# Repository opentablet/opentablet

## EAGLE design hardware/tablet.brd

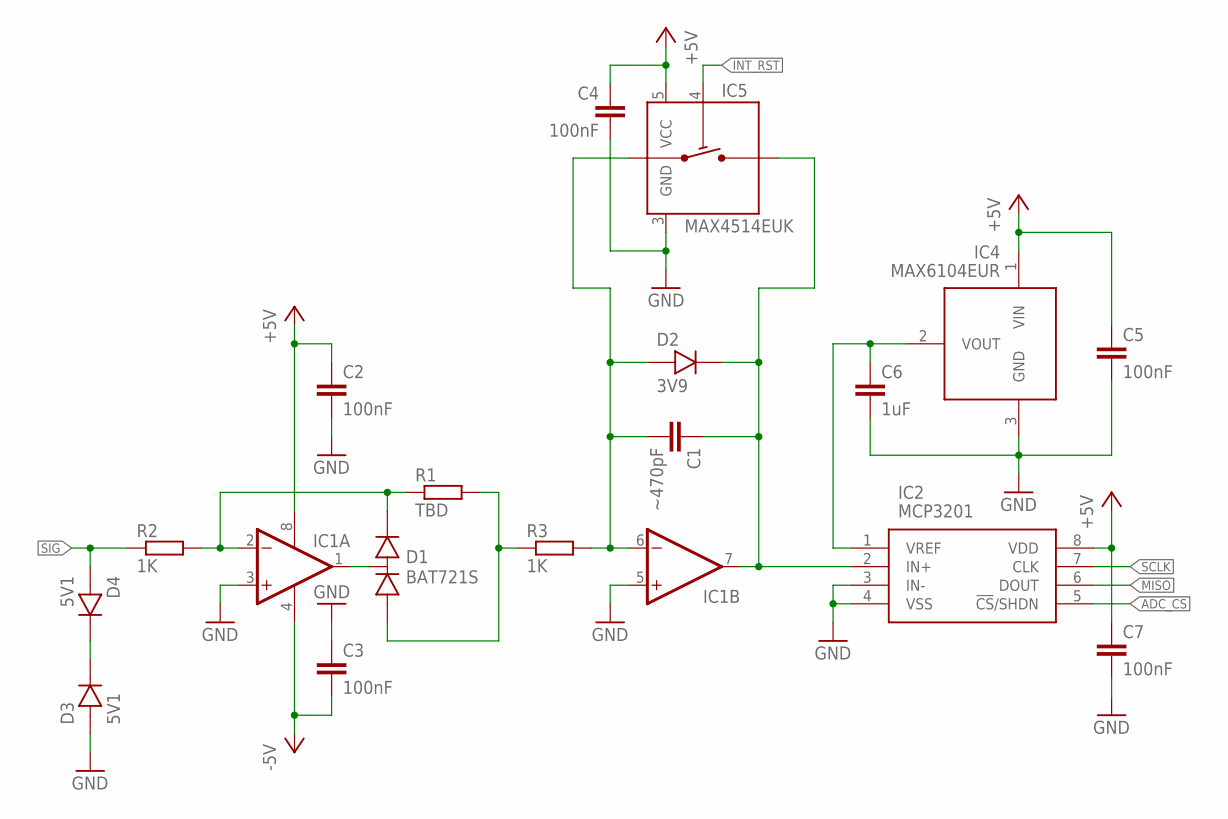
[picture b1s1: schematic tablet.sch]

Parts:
C1: ~470pF; 0603
C2, C3, C4, C5, C7: 100nF; 0603
C6: 1uF; 0603
D1: BAT721S; SOT23_3
D2: 3V9; SOD323
D3, D4: 5V1; SOD323
IC1: OPAMP_DUALSOIC8; SOIC8
IC2: MCP3201; SOIC8
IC4: MAX6104EUR; SOT23_3
IC5: MAX4514EUK; SOT23_5
R1: TBD; 0603
R2, R3: 1K; 0603

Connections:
+5V: C2.1, C4.1, C5.1, C7.1, IC1.8 (V+), IC2.8 (VDD), IC4.1 (VIN), IC5.5 (VCC)
-5V: C3.2, IC1.4 (V-)
ADC_CS: IC2.5 (!CS!/SHDN)
GND: C2.2, C3.1, C4.2, C5.2, C6.2, C7.2, D3.1, IC1.3 (+IN), IC1.5 (+IN), IC2.3 (IN-), IC2.4 (VSS), IC4.3 (GND), IC5.3 (GND)
INT_RST: IC5.4 (IN)
MISO: IC2.6 (DOUT)
unnamed: D1.1 (A), R1.2, R3.1
unnamed: D1.2 (C), IC1.2 (-IN), R1.1, R2.2
unnamed: D1.3 (COM), IC1.1 (OUT)
unnamed: C1.2, D2.1, IC1.6 (-IN), IC5.1 (COM), R3.2
unnamed: D3.2, D4.2
unnamed: C6.1, IC2.1 (VREF), IC4.2 (VOUT)
SCLK: IC2.7 (CLK)
SIG: D4.1, R2.1
VOUT: C1.1, D2.2, IC1.7 (OUT), IC2.2 (IN+), IC5.2 (NO)

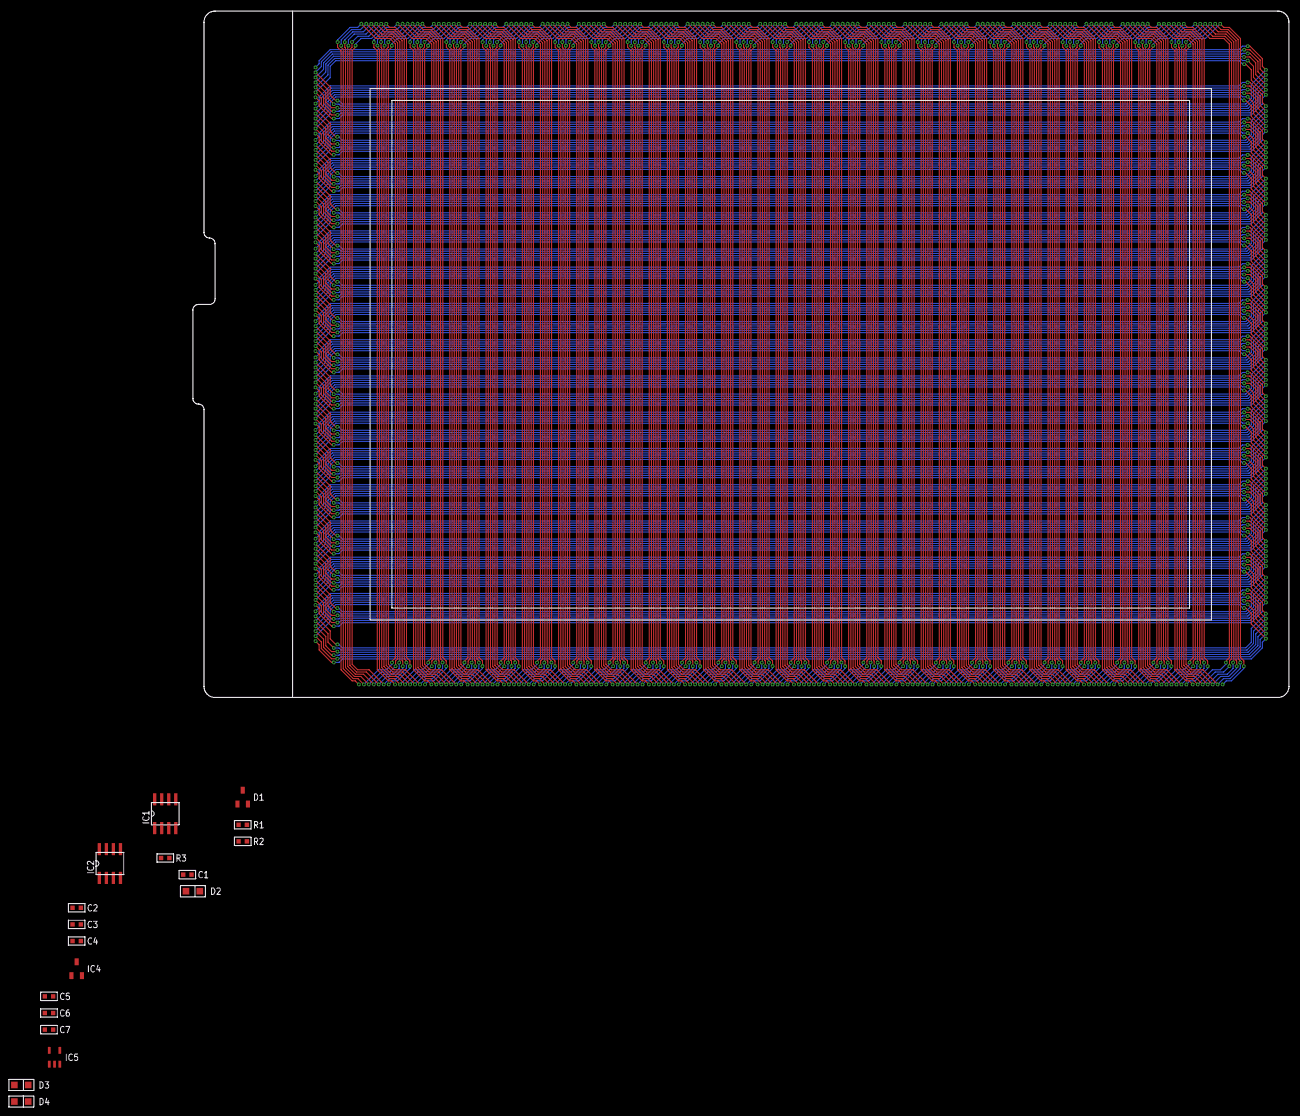
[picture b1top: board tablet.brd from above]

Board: 2 copper layers, 198.0 x 124.0 mm, 18 parts (0 on the bottom side), 11 nets.

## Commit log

2022-04-08 Add .gitignore
2022-04-08 Setup board outline and design rules
2022-04-09 Add temp schematic files to .gitignore
2022-04-09 Initial analog front end schematic
2022-04-09 Simplify analog switch layout and increase analog ref load capacitance to ensure stability
2022-04-10 Add protection diodes to common signal
2022-04-11 Fix precision rectifier op amp orientation
2022-04-23 Draft coil layout
